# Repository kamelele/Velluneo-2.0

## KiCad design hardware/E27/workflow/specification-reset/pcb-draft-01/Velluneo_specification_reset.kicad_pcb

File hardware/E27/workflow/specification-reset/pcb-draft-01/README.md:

# PCB-DRAFT-01 — native driver PCB editing has started

18 November 2026. Base7b75131667252634584552b4094c608cd88b9f2a. The owner explicitly requested starting PCB work and continued driver engineering. This packet contains a real native editable KiCad10.0.6 PCB, not another drawn packing plan. It is an **unrouted engineering workspace**, not accepted schematic/placement/routing, manufacturing release or an operating qualified supply.

## Open the actual board

Download Velluneo_driver_PCB_draft.zip, extract it, open Velluneo_specification_reset.kicad_pro and then its PCB editor. The archive includes matched schematic/PCB, local symbol/footprint libraries, proposed rules and all envelope3Dmodels; it needs no external library/model download. The repository board uses the original basename in this isolated packet; local library tables point to ../libraries. The portable archive changes only those table URIs to its included libraries folder.

There are31components/79physicalpads,22functionalnets and4individual KiCad synthetic NC nets for T1.3/7/8/9. Those singleton nets do not introduce connections to the unwound terminals. Symbol UUID association, values, MPN fields, footprint IDs and physical membership match the saved schematic. PCB netnames use the native KiCad labels/auto-names; build-result.json records the complete logical-to-native mapping. All four sides of the32x60mmoutline are native Edge.Cuts; thickness is1.6mm/two copper layers. The proposed2oz/ENIG manufacturing route remains unconfirmed; this workspace is not a verified stackup or supplier order.

The final driver-entry-02 component coordinates and sides are transferred exactly, with100mmoffset. In particular, C2 is behind U1 and no semiconductor courtyard overlaps the30x30T1allocation. Models are explicit project body/envelope allocations from retained native F.Fab bounds and installed-height proposals. The T1bluebox is a required30x30x18mm allocation, not a finished verified transformer. C1 is an explicit cylindrical mesh,10.5mmdiameter and22.5mminstalled allocation. A first native render omitted the VRML cylinder primitive; an explicit mesh corrected the display. Native renders of both sides were visually inspected after that correction. Other models are bounding prisms, not vendor STEP models.

## Isolation and functional spacing in the actual file

A real F.Cu/B.Cu rule area spans globalY83.100..93.025mm across the board. New tracks, pads, vias and pours are prohibited there. A scoped candidate clearance rule reserves10mm nominal between primary/secondary functional and NC-row nets. Actual native geometry gives10.225mm minimum projected pad-box distance; subtracting the proposed0.35mmper-domain solder/position allowance leaves9.525mm, not10mmfinished metal clearance.

The design contract uses the legitimate TI SLUP419p10 telecommunications worked example only as a planning-method reference. Its400VDC example is not a400Vrms lighting approval. Actual working RMS, repetitive peaks,106kHz assessment, air/surface/solid paths, CTI/material/process and IEC61347/60598 branch remain unresolved. No coating/mask credit, unlicensed standard, transferred certification or nonexistent insulation test is used. No slot is selected. Core/yokes are primary-hazard objects until their completed construction is assessed.

A separate proposed3mmprimary-HV-to-quiet rule deliberately exposes unfinished primary layout and inherent package spacing. It is an engineering screening rule, not a justified normative blanket limit. Its37clearance findings remain visible; there are no exceptions or exclusions added to hide them. A voltage-/object-specific assessment is required before adopting final rules. The previous all-position pad-box pass did not assess these local functional spacings.

## Actual checks

- Saved/reloaded native board:31footprints/79pads; all expected physical net sets and4NCsingletons match; all MPN/value fields, model paths and rectangle dimensions checked. Maximum pad-box difference from the prior independent proposal is about7.11e-15mm.
- Native schematic/PCB parity: **zero findings** after correcting native net aliases and matching the actual Description/MPN fields. No pin-type, NC or circuit changes were used.
- Native DRC: **exit5**,37clearance,3silk-edge,5silk-overlap and6silk-over-copper findings;53unconnecteditems. The board has zero routed tracks/vias and is not DRC-clean. Existing native default ignored checks remain listed; no new suppression was introduced.
- Fresh installed toolkit doctor and intended-graph comparison pass; native all-severity ERC reports zero findings. Actual schematic requirementsU05-U09 still exit1 and work check exits2 configuration_error. The isolated draft does not silently adopt managed configuration or change those results.
- Native SVG and ray-traced3D exports were executed on the saved board. Preview composition uses the actual native pixels, not AI imagery or fictional copper.

Full command/status records and actual native reports are in checks/. Every result has limited scope; passing parity/geometry does not establish electrical behavior or safety.

## Startup, protection and transformer design work

design-contract.json records exact retained UCC28711 source limits and executable calculations: VDD steady9–35V, start19–23V/off7.7–8.5V; static normal/backup CS screens0.34910/0.68959A;48.31mAideal current ramp during280nsblanking at the chosen high-line/Lp corner. These are not proven dynamic fault peaks. The source startup minimum is atVDD0/HV100V; no complete HV-source charging law or minimum fault-discharge current is supplied by those table points. No guaranteed retry spacing or11Wfault ceiling is invented. NTC pin3 interface thresholds are explicit; RT1-open thermal safety remains open.

The active31-position circuit and R1 regularAC05 are preserved. The previously sourced safety-fusible candidate remains unapplied: its230Vac fusing test does not qualify207–253Vac/hot-repeated-charge coordination. No NRND-reference controller or unmatched transformer is silently substituted. The read-only reference audit found materially different CV ceilings/current programming/thermal coverage, so rebuilding around them would be a real ECO, not a shortcut.

T1 retains P1→5/A2→4/S6→10 and four unwound pins. Raw1.35mmfinishedholes/2.4mmpads,5mmpitch/22.5mmrows and the source pin projection are retained. The C2 winding/material/cut-length/DCR contract remains the manufacturing proposal. Finished yoke registration, primary bridge, TIW exit/bend/termination zones and tolerances are still missing. The raw footprint courtyard is not a finishedT1courtyard. The whole30x30keepout on both copper sides suggested by an implementer was not adopted blindly: it would invalidate the present passive placement and does not establish the missing metal/leadout geometry. Actual finished construction can require a placement/footprint revision. No2mmstandoff is added.

## Stage distinction and next design work

The earlier coordinator treated supplier/physical-test/full-qualification needs too broadly as a prohibition on authoring any PCB. The actual requirements permit engineering design with explicit provisional inputs. This corrects that mistake, not the technical source limits. gate-audit.md gives the exact distinction. The current owner instruction authorizes this working draft; it is not recorded as approving the unresolved schematic stage. No approval field or unknown requirement was changed.

The next CAD work is to resolve the local HV/quiet and sensitive return/loop placement findings, then route using an approved spatial/rule contract after the genuine stage decisions. Startup/fault/NTC-open design, input coordination, finishedT1/insulation, thermal boundary, wire/lead-form/process and materials still need closure before their respective acceptance gates. No final Gerbers, fabrication, powered test or order is authorized. Native PCB editing has started; full driver qualification has not been completed.

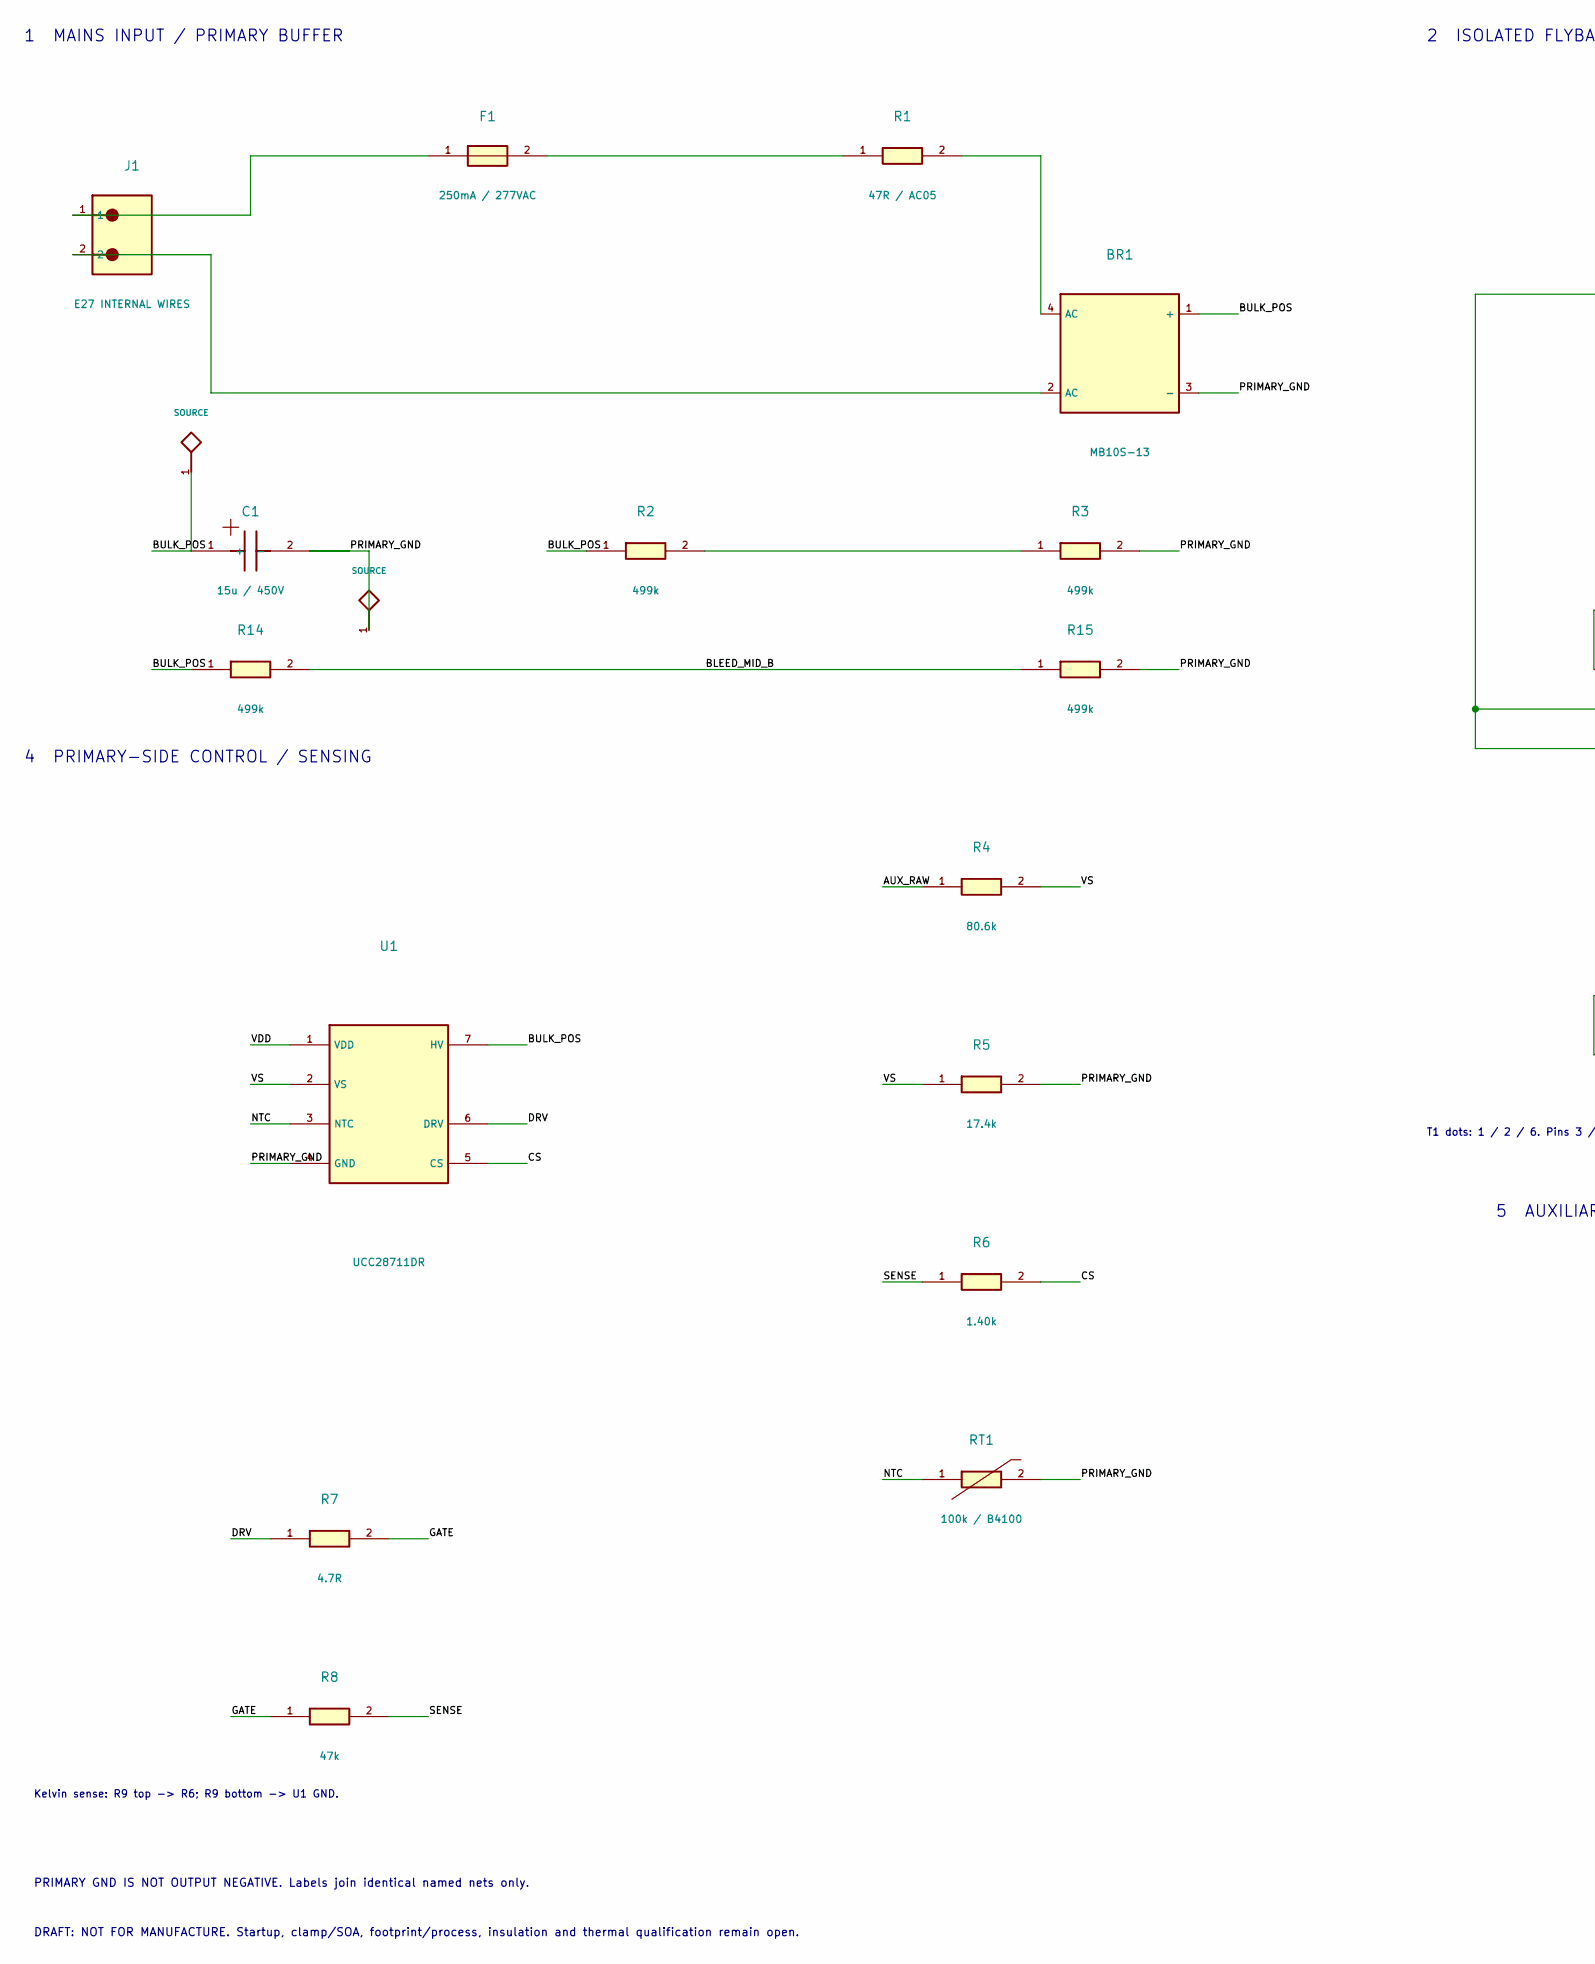
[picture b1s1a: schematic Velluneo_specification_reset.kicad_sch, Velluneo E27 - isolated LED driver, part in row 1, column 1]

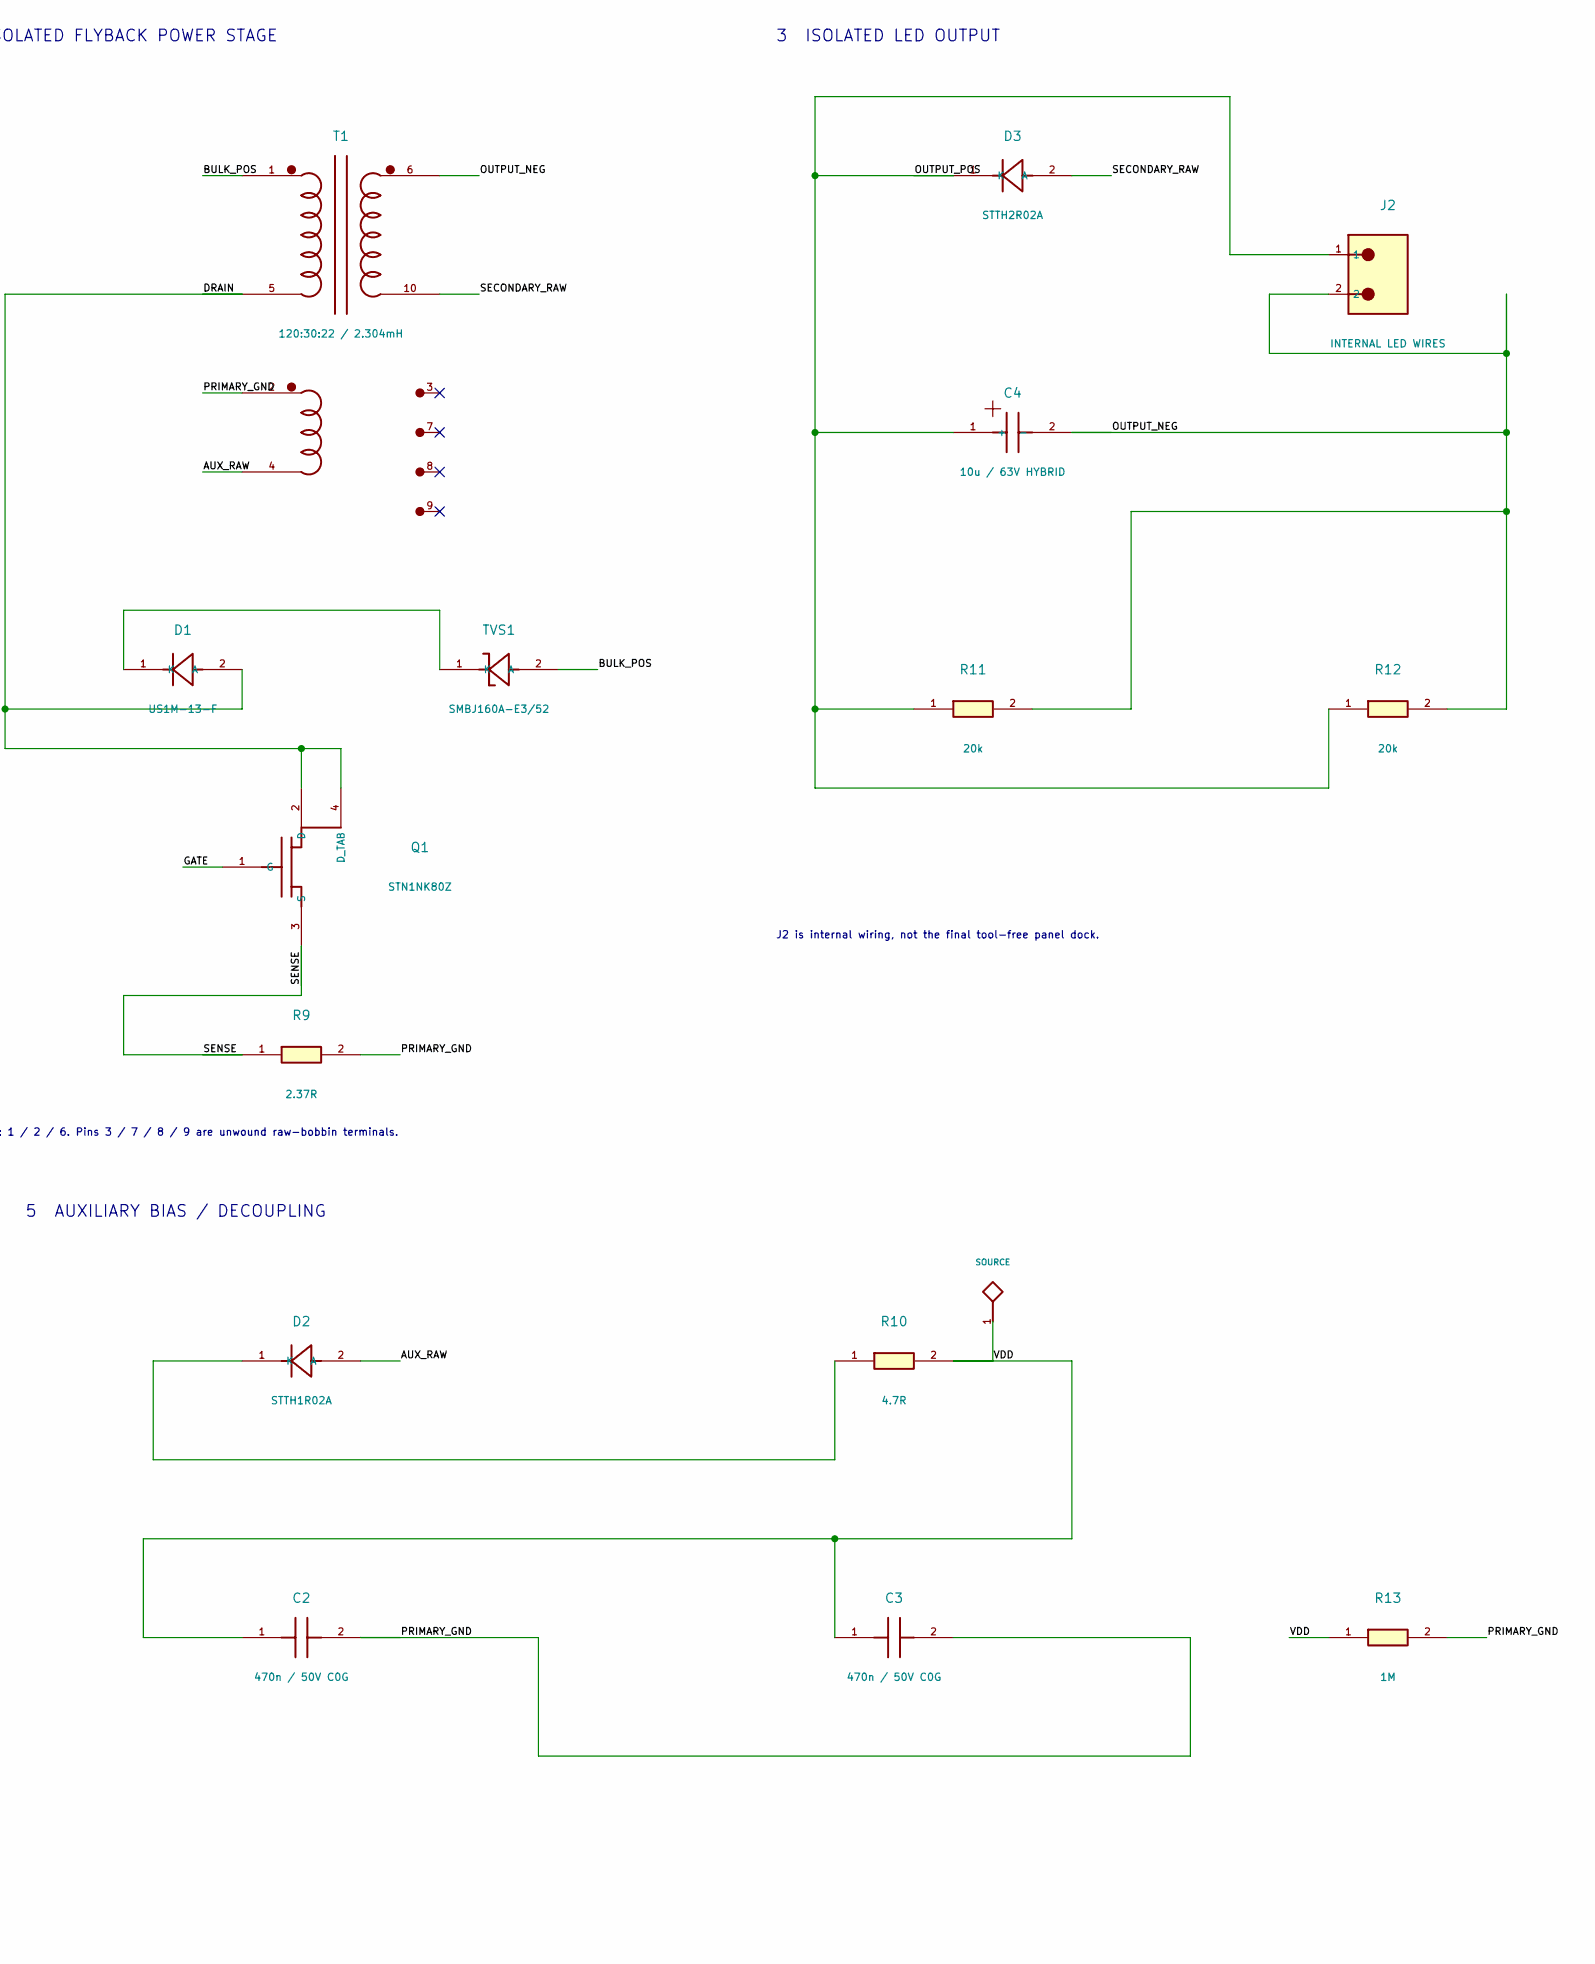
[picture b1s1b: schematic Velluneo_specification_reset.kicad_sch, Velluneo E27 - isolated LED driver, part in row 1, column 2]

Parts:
BR1: MB10S-13; MB10S_Diodes_MBS_1P_2AC_3N_4AC; MPN MB10S-13
C1: 15u / 450V; Rubycon_BXW_D10_P5_PROJECT_CANDIDATE; MPN 450BXW15MEFR10X20
C2, C3: 470n / 50V C0G; KEMET_2220_C0G_DensityB_Native; MPN C2220C474J5GACTU
C4: 10u / 63V HYBRID; Panasonic_ZA_D_Standard_Native; MPN EEHZA1J100P
D1: US1M-13-F; Diodes_US1M_SMA_Native; MPN US1M-13-F
D2: STTH1R02A; ST_STTH_SMA_Native; MPN STTH1R02A
D3: STTH2R02A; ST_STTH_SMA_Native; MPN STTH2R02A
F1: 250mA / 277VAC; SCHURTER_UMTH_WEB_PROVISIONAL; MPN 3403.0268.23
J1: E27 INTERNAL WIRES; InternalWirePair_P7p62_D1p6_PROJECT_CANDIDATE; MPN PROJECT:INSULATED_INPUT_WIRE_PADS
J2: INTERNAL LED WIRES; InternalWirePair_P7p62_D1p6_PROJECT_CANDIDATE; MPN PROJECT:INSULATED_OUTPUT_WIRE_PADS
Q1: STN1NK80Z; STN1NK80Z_SOT223_Tab4; MPN STN1NK80Z
R1: 47R / AC05; AC05_P25p4_FORMED_PROJECT_CANDIDATE; MPN AC05000004709JAC00
R2, R3, R14, R15: 499k; CRCW_2512_NativeReflow; MPN CRCW2512499KFKEG
R4: 80.6k; CRCW_0805_NativeReflow; MPN CRCW080580K6FKEA
R5: 17.4k; CRCW_0805_NativeReflow; MPN CRCW080517K4FKEA
R6: 1.40k; CRCW_0603_NativeReflow; MPN CRCW06031K40FKEA
R7: 4.7R; CRCW_0805_NativeReflow; MPN CRCW08054R70FKEA
R8: 47k; CRCW_0603_NativeReflow; MPN CRCW060347K0FKEA
R9: 2.37R; CRCW_1206_NativeReflow_ClippedSilk; MPN CRCW12062R37FKEA
R10: 4.7R; CRCW_2512_NativeReflow; MPN CRCW25124R70FKEG
R11, R12: 20k; CRCW_2512_NativeReflow; MPN CRCW251220K0FKEG
R13: 1M; CRCW_0603_NativeReflow; MPN CRCW06031M00FKEA
RT1: 100k / B4100; NTCS0603_NativeReflow; MPN NTCS0603E3104FXT
T1: 120:30:22 / 2.304mH; TDK_B66422W1010D001_EFD25_RAW_CANDIDATE; MPN CUSTOM:EFD25_120_30_22
TVS1: SMBJ160A-E3/52; Vishay_SMBJ_PROJECT_CANDIDATE; MPN SMBJ160A-E3/52
U1: UCC28711DR; UCC28711DR_SOIC7_HV7; MPN UCC28711DR

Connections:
/AUX_RAW: D2.2 (A), R4.1, T1.4
/BLEED_MID_B: R14.2, R15.1
/BULK_POS: BR1.1 (+), C1.1 (+), R2.1, R14.1, T1.1, TVS1.2 (A), U1.7 (HV)
/CS: R6.2, U1.5 (CS)
/DRAIN: D1.2 (A), Q1.2 (D), Q1.4 (D_TAB), T1.5
/DRV: R7.1, U1.6 (DRV)
/GATE: Q1.1 (G), R7.2, R8.1
/NTC: RT1.1, U1.3 (NTC)
/OUTPUT_NEG: C4.2 (-), J2.2, R11.2, R12.2, T1.6
/OUTPUT_POS: C4.1 (+), D3.1 (K), J2.1, R11.1, R12.1
/PRIMARY_GND: BR1.3 (-), C1.2 (-), C2.2, C3.2, R3.2, R5.2, R9.2, R13.2, R15.2, RT1.2, T1.2, U1.4 (GND)
/SECONDARY_RAW: D3.2 (A), T1.10
/SENSE: Q1.3 (S), R6.1, R8.2, R9.1
/VDD: C2.1, C3.1, R10.2, R13.1, U1.1 (VDD)
/VS: R4.2, R5.1, U1.2 (VS)
unnamed: BR1.2 (AC), J1.2
unnamed: BR1.4 (AC), R1.2
unnamed: D1.1 (K), TVS1.1 (K)
unnamed: D2.1 (K), R10.1
unnamed: F1.1, J1.1
unnamed: F1.2, R1.1
unnamed: R2.2, R3.1

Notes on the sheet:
1 MAINS INPUT / PRIMARY BUFFER
2 ISOLATED FLYBACK POWER STAGE
3 ISOLATED LED OUTPUT
4 PRIMARY-SIDE CONTROL / SENSING
5 AUXILIARY BIAS / DECOUPLING
PRIMARY GND IS NOT OUTPUT NEGATIVE. Labels join identical named nets only.
DRAFT: NOT FOR MANUFACTURE. Startup, clamp/SOA, footprint/process, insulation and thermal qualification remain open.
T1 dots: 1 / 2 / 6. Pins 3 / 7 / 8 / 9 are unwound raw-bobbin terminals.
J2 is internal wiring, not the final tool-free panel dock.
Kelvin sense: R9 top -> R6; R9 bottom -> U1 GND.

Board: 2 copper layers, 31 parts (22 on the bottom side), 22 nets, no tracks yet.
